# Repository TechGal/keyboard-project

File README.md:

# keyboard-project
Files for my first mechanical keyboard!

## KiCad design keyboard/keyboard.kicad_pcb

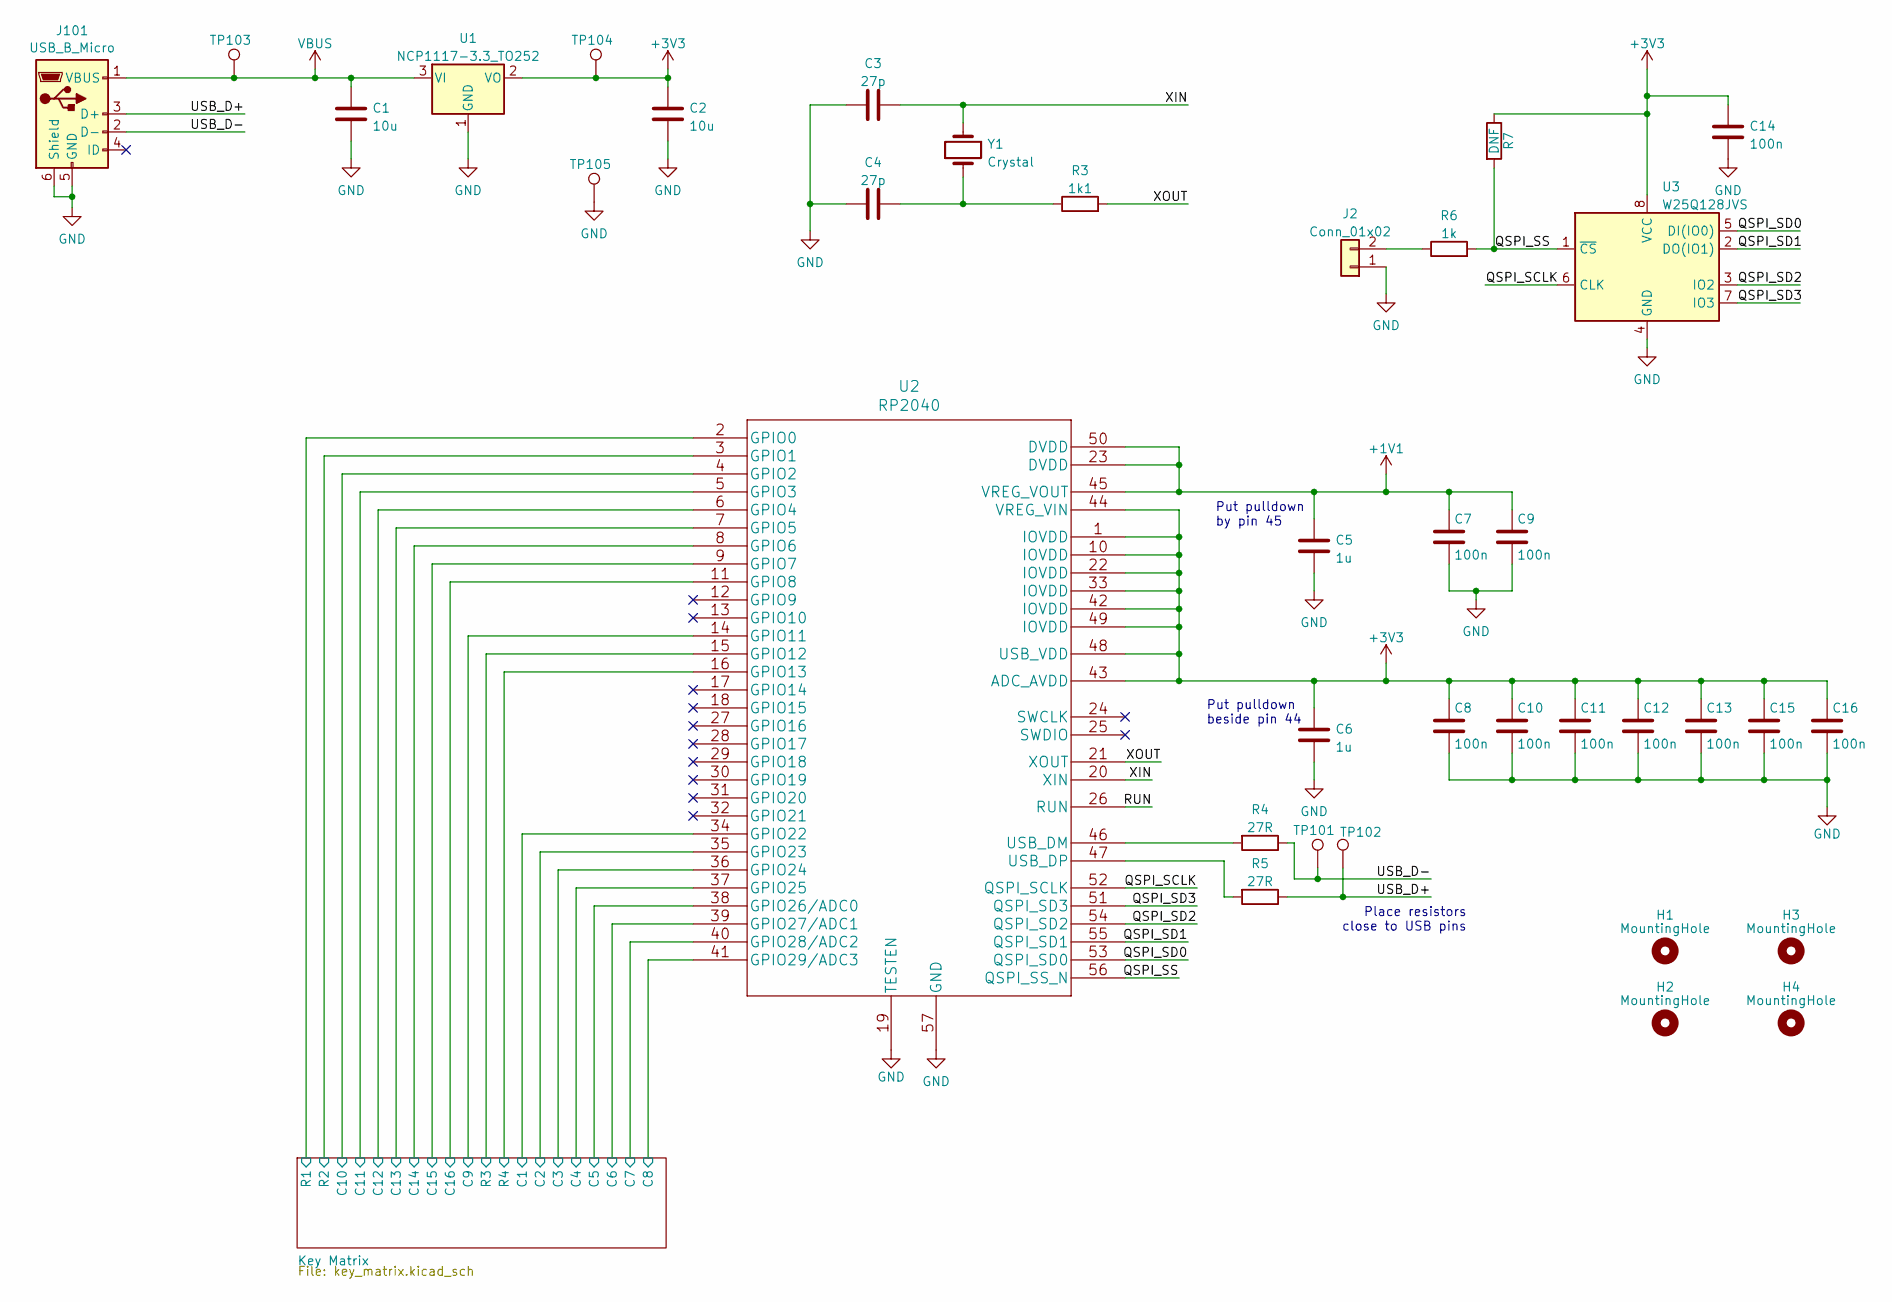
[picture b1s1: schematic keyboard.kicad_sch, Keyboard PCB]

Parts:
C1, C2: 10u; C_0603_1608Metric_Pad1.08x0.95mm_HandSolder
C3, C4: 27p; C_0603_1608Metric_Pad1.08x0.95mm_HandSolder
C5, C6: 1u; C_0603_1608Metric_Pad1.08x0.95mm_HandSolder
C7, C8, C9, C10, C11, C12, C13, C14, C15, C16: 100n; C_0603_1608Metric_Pad1.08x0.95mm_HandSolder
H1, H2, H3, H4: MountingHole; MountingHole_4.3mm_M4_Pad
J2: Conn_01x02; PinHeader_1x02_P2.54mm_Horizontal
J101: USB_B_Micro; USB_Micro-AB_Molex_47590-0001
R3: 1k1; R_0603_1608Metric_Pad0.98x0.95mm_HandSolder
R4, R5: 27R; R_0603_1608Metric_Pad0.98x0.95mm_HandSolder
R6: 1k; R_0603_1608Metric_Pad0.98x0.95mm_HandSolder
R7: DNF; R_0603_1608Metric_Pad0.98x0.95mm_HandSolder
TP101, TP102, TP103, TP104, TP105: TestPoint_THTPad_D1.0mm_Drill0.5mm
U1: NCP1117-3.3_TO252; TO-252-2
U2: RP2040; RP2040-QFN-56
U3: W25Q128JVS; SOIC-8_5.23x5.23mm_P1.27mm
Y1: Crystal; Crystal_HC18-U_Vertical

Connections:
+1V1: C5.1, C7.1, C9.1, U2.23 (DVDD), U2.45 (VREG_VOUT), U2.50 (DVDD)
+3V3: C2.1, C6.1, C8.1, C10.1, C11.1, C12.1, C13.1, C14.1, C15.1, C16.1, R7.1, TP104.1, U1.2 (VO), U2.1 (IOVDD), U2.10 (IOVDD), U2.22 (IOVDD), U2.33 (IOVDD), U2.42 (IOVDD), U2.43 (ADC_AVDD), U2.44 (VREG_VIN), U2.48 (USB_VDD), U2.49 (IOVDD), U3.8 (VCC)
/Key Matrix/C1: U2.34 (GPIO22); also elsewhere on the board
/Key Matrix/C2: U2.35 (GPIO23); also elsewhere on the board
/Key Matrix/C3: U2.36 (GPIO24); also elsewhere on the board
/Key Matrix/C4: U2.37 (GPIO25); also elsewhere on the board
/Key Matrix/C5: U2.38 (GPIO26/ADC0); also elsewhere on the board
/Key Matrix/C6: U2.39 (GPIO27/ADC1); also elsewhere on the board
/Key Matrix/C7: U2.40 (GPIO28/ADC2); also elsewhere on the board
/Key Matrix/C8: U2.41 (GPIO29/ADC3); also elsewhere on the board
/Key Matrix/C9: U2.14 (GPIO11); also elsewhere on the board
/Key Matrix/C10: U2.4 (GPIO2); also elsewhere on the board
/Key Matrix/C11: U2.5 (GPIO3); also elsewhere on the board
/Key Matrix/C12: U2.6 (GPIO4); also elsewhere on the board
/Key Matrix/C13: U2.7 (GPIO5); also elsewhere on the board
/Key Matrix/C14: U2.8 (GPIO6); also elsewhere on the board
/Key Matrix/C15: U2.9 (GPIO7); also elsewhere on the board
/Key Matrix/C16: U2.11 (GPIO8); also elsewhere on the board
/Key Matrix/R1: U2.2 (GPIO0); also elsewhere on the board
/Key Matrix/R2: U2.3 (GPIO1); also elsewhere on the board
/Key Matrix/R3: U2.15 (GPIO12); also elsewhere on the board
/Key Matrix/R4: U2.16 (GPIO13); also elsewhere on the board
/QSPI_SCLK: U2.52 (QSPI_SCLK), U3.6 (CLK)
/QSPI_SD0: U2.53 (QSPI_SD0), U3.5 (DI(IO0))
/QSPI_SD1: U2.55 (QSPI_SD1), U3.2 (DO(IO1))
/QSPI_SD2: U2.54 (QSPI_SD2), U3.3 (IO2)
/QSPI_SD3: U2.51 (QSPI_SD3), U3.7 (IO3)
/QSPI_SS: R6.2, R7.2, U2.56 (QSPI_SS_N), U3.1 (~CS)
/RUN: U2.26 (RUN)
/USB_D+: J101.3 (D+), R5.1, TP102.1
/USB_D-: J101.2 (D-), R4.1, TP101.1
/XIN: C3.2, U2.20 (XIN), Y1.2
/XOUT: R3.2, U2.21 (XOUT)
GND: C1.2, C2.2, C3.1, C4.1, C5.2, C6.2, C7.2, C8.2, C9.2, C10.2, C11.2, C12.2, C13.2, C14.2, C15.2, C16.2, J2.1, J101.5 (GND), J101.6 (Shield), TP105.1, U1.1 (GND), U2.19 (TESTEN), U2.57 (GND), U3.4 (GND)
unnamed: C4.2, R3.1, Y1.1
unnamed: J2.2, R6.1
unnamed: R4.2, U2.46 (USB_DM)
unnamed: R5.2, U2.47 (USB_DP)
VBUS: C1.1, J101.1 (VBUS), TP103.1, U1.3 (VI)

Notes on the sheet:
Put pulldown beside pin 44
Put pulldown by pin 45
Place resistors close to USB pins

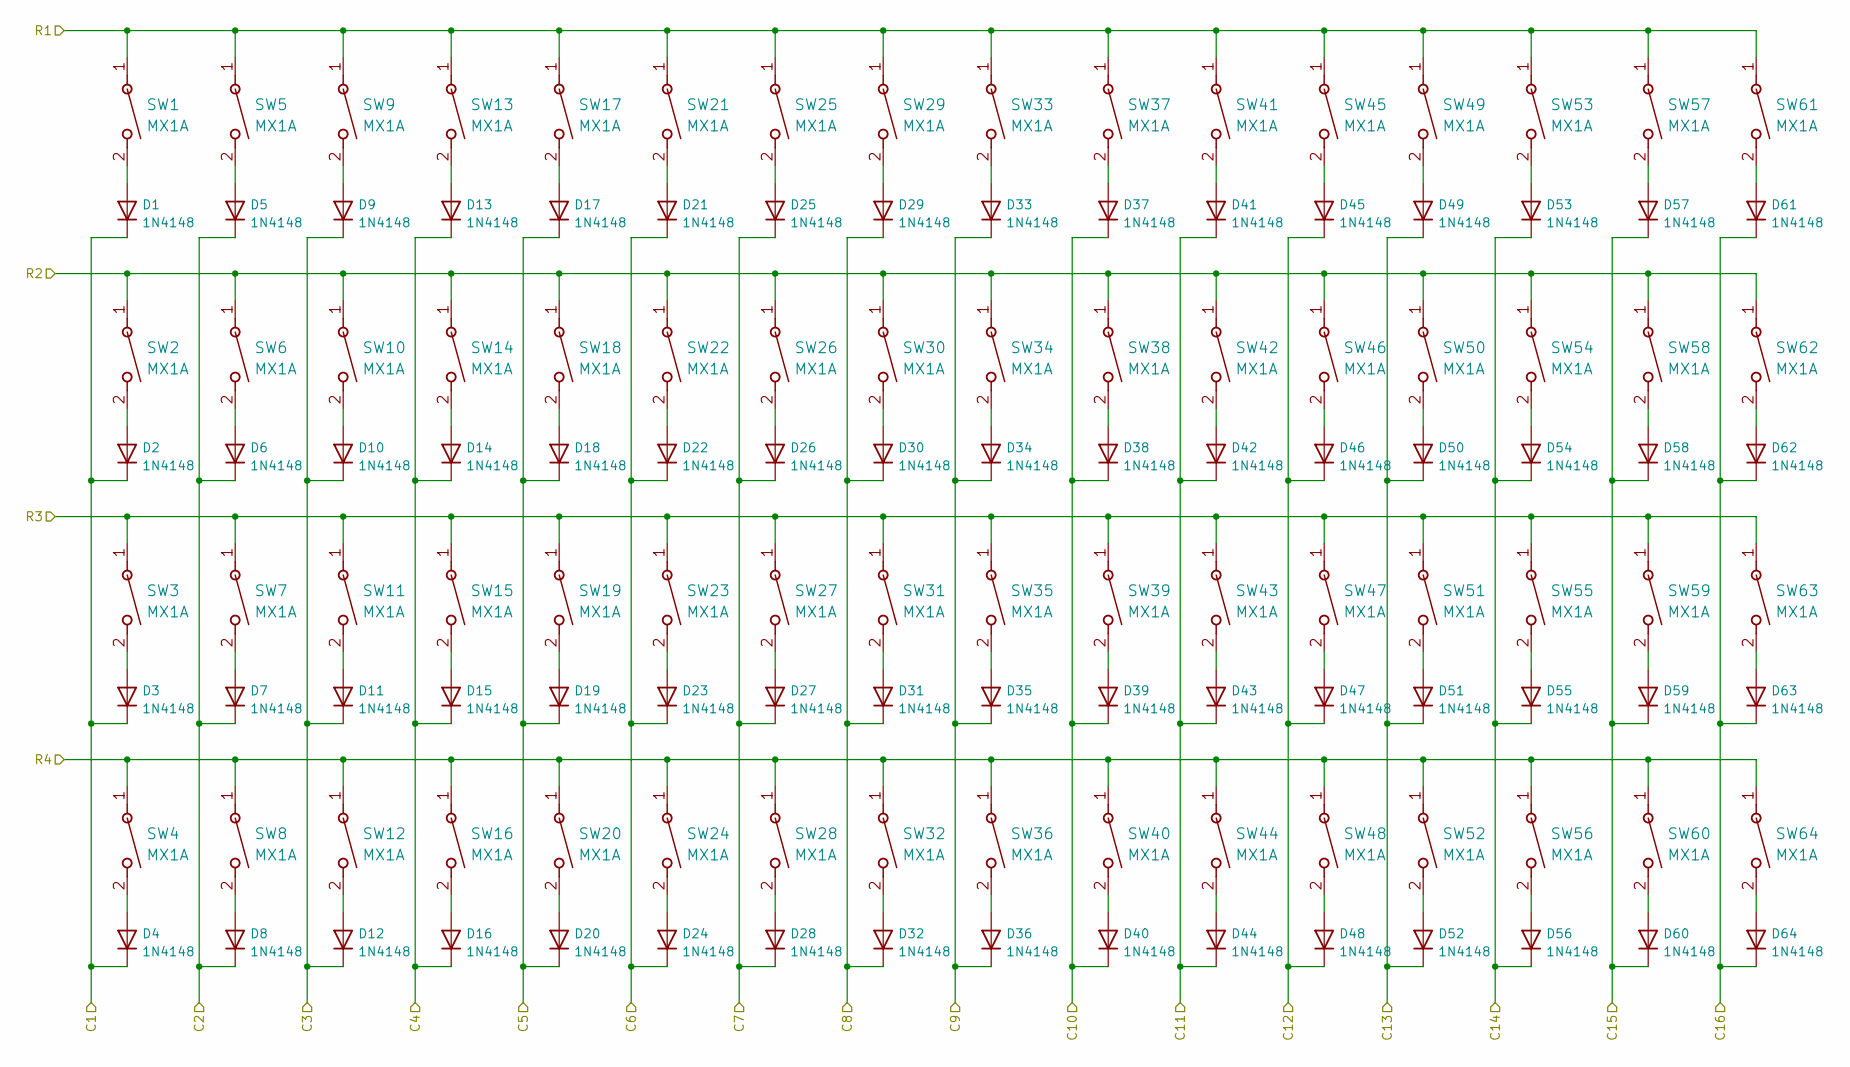
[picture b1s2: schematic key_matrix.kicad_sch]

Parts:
D1, D2, D3, D4, D5, D6, D7, D8, D9, D10, D11, D12, D13, D14, D15, D16, D17, D18, D19, D20, D21, D22, D23, D24, D25, D26, D27, D28, D29, D30, D31, D32, D33, D34, D35, D36, D37, D38, D39, D40, D41, D42, D43, D44, D45, D46, D47, D48, D49, D50, D51, D52, D53, D54, D55, D56, D57, D58, D59, D60, D61, D62, D63, D64: 1N4148; D_0805_2012Metric_Pad1.15x1.40mm_HandSolder
SW1, SW2, SW3, SW4, SW5, SW6, SW7, SW8, SW9, SW10, SW11, SW12, SW13, SW14, SW15, SW16, SW17, SW18, SW19, SW20, SW21, SW22, SW23, SW24, SW25, SW26, SW27, SW28, SW29, SW30, SW31, SW32, SW33, SW34, SW35, SW36, SW37, SW38, SW39, SW40, SW41, SW42, SW43, SW44, SW45, SW46, SW47, SW48, SW49, SW50, SW51, SW52, SW53, SW54, SW55, SW56, SW57, SW58, SW59, SW60, SW61, SW62, SW63, SW64: MX1A; SW_Cherry_MX_1.00u_PCB

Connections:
/Key Matrix/C1: D1.1 (K), D2.1 (K), D3.1 (K), D4.1 (K); also elsewhere on the board
/Key Matrix/C2: D5.1 (K), D6.1 (K), D7.1 (K), D8.1 (K); also elsewhere on the board
/Key Matrix/C3: D9.1 (K), D10.1 (K), D11.1 (K), D12.1 (K); also elsewhere on the board
/Key Matrix/C4: D13.1 (K), D14.1 (K), D15.1 (K), D16.1 (K); also elsewhere on the board
/Key Matrix/C5: D17.1 (K), D18.1 (K), D19.1 (K), D20.1 (K); also elsewhere on the board
/Key Matrix/C6: D21.1 (K), D22.1 (K), D23.1 (K), D24.1 (K); also elsewhere on the board
/Key Matrix/C7: D25.1 (K), D26.1 (K), D27.1 (K), D28.1 (K); also elsewhere on the board
/Key Matrix/C8: D29.1 (K), D30.1 (K), D31.1 (K), D32.1 (K); also elsewhere on the board
/Key Matrix/C9: D33.1 (K), D34.1 (K), D35.1 (K), D36.1 (K); also elsewhere on the board
/Key Matrix/C10: D37.1 (K), D38.1 (K), D39.1 (K), D40.1 (K); also elsewhere on the board
/Key Matrix/C11: D41.1 (K), D42.1 (K), D43.1 (K), D44.1 (K); also elsewhere on the board
/Key Matrix/C12: D45.1 (K), D46.1 (K), D47.1 (K), D48.1 (K); also elsewhere on the board
/Key Matrix/C13: D49.1 (K), D50.1 (K), D51.1 (K), D52.1 (K); also elsewhere on the board
/Key Matrix/C14: D53.1 (K), D54.1 (K), D55.1 (K), D56.1 (K); also elsewhere on the board
/Key Matrix/C15: D57.1 (K), D58.1 (K), D59.1 (K), D60.1 (K); also elsewhere on the board
/Key Matrix/C16: D61.1 (K), D62.1 (K), D63.1 (K), D64.1 (K); also elsewhere on the board
/Key Matrix/R1: SW1.1, SW5.1, SW9.1, SW13.1, SW17.1, SW21.1, SW25.1, SW29.1, SW33.1, SW37.1, SW41.1, SW45.1, SW49.1, SW53.1, SW57.1, SW61.1; also elsewhere on the board
/Key Matrix/R2: SW2.1, SW6.1, SW10.1, SW14.1, SW18.1, SW22.1, SW26.1, SW30.1, SW34.1, SW38.1, SW42.1, SW46.1, SW50.1, SW54.1, SW58.1, SW62.1; also elsewhere on the board
/Key Matrix/R3: SW3.1, SW7.1, SW11.1, SW15.1, SW19.1, SW23.1, SW27.1, SW31.1, SW35.1, SW39.1, SW43.1, SW47.1, SW51.1, SW55.1, SW59.1, SW63.1; also elsewhere on the board
/Key Matrix/R4: SW4.1, SW8.1, SW12.1, SW16.1, SW20.1, SW24.1, SW28.1, SW32.1, SW36.1, SW40.1, SW44.1, SW48.1, SW52.1, SW56.1, SW60.1, SW64.1; also elsewhere on the board
unnamed: D1.2 (A), SW1.2
unnamed: D2.2 (A), SW2.2
unnamed: D3.2 (A), SW3.2
unnamed: D4.2 (A), SW4.2
unnamed: D5.2 (A), SW5.2
unnamed: D6.2 (A), SW6.2
unnamed: D7.2 (A), SW7.2
unnamed: D8.2 (A), SW8.2
unnamed: D9.2 (A), SW9.2
unnamed: D10.2 (A), SW10.2
unnamed: D11.2 (A), SW11.2
unnamed: D12.2 (A), SW12.2
unnamed: D13.2 (A), SW13.2
unnamed: D14.2 (A), SW14.2
unnamed: D15.2 (A), SW15.2
unnamed: D16.2 (A), SW16.2
unnamed: D17.2 (A), SW17.2
unnamed: D18.2 (A), SW18.2
unnamed: D19.2 (A), SW19.2
unnamed: D20.2 (A), SW20.2
unnamed: D21.2 (A), SW21.2
unnamed: D22.2 (A), SW22.2
unnamed: D23.2 (A), SW23.2
unnamed: D24.2 (A), SW24.2
unnamed: D25.2 (A), SW25.2
unnamed: D26.2 (A), SW26.2
unnamed: D27.2 (A), SW27.2
unnamed: D28.2 (A), SW28.2
unnamed: D29.2 (A), SW29.2
unnamed: D30.2 (A), SW30.2
unnamed: D31.2 (A), SW31.2
unnamed: D32.2 (A), SW32.2
unnamed: D33.2 (A), SW33.2
unnamed: D34.2 (A), SW34.2
unnamed: D35.2 (A), SW35.2
unnamed: D36.2 (A), SW36.2
unnamed: D37.2 (A), SW37.2
unnamed: D38.2 (A), SW38.2
unnamed: D39.2 (A), SW39.2
unnamed: D40.2 (A), SW40.2
unnamed: D41.2 (A), SW41.2
unnamed: D42.2 (A), SW42.2
unnamed: D43.2 (A), SW43.2
unnamed: D44.2 (A), SW44.2
unnamed: D45.2 (A), SW45.2
unnamed: D46.2 (A), SW46.2
unnamed: D47.2 (A), SW47.2
unnamed: D48.2 (A), SW48.2
unnamed: D49.2 (A), SW49.2
unnamed: D50.2 (A), SW50.2
unnamed: D51.2 (A), SW51.2
unnamed: D52.2 (A), SW52.2
unnamed: D53.2 (A), SW53.2
unnamed: D54.2 (A), SW54.2
unnamed: D55.2 (A), SW55.2
unnamed: D56.2 (A), SW56.2
unnamed: D57.2 (A), SW57.2
unnamed: D58.2 (A), SW58.2
unnamed: D59.2 (A), SW59.2
unnamed: D60.2 (A), SW60.2
unnamed: D61.2 (A), SW61.2
unnamed: D62.2 (A), SW62.2
unnamed: D63.2 (A), SW63.2
unnamed: D64.2 (A), SW64.2

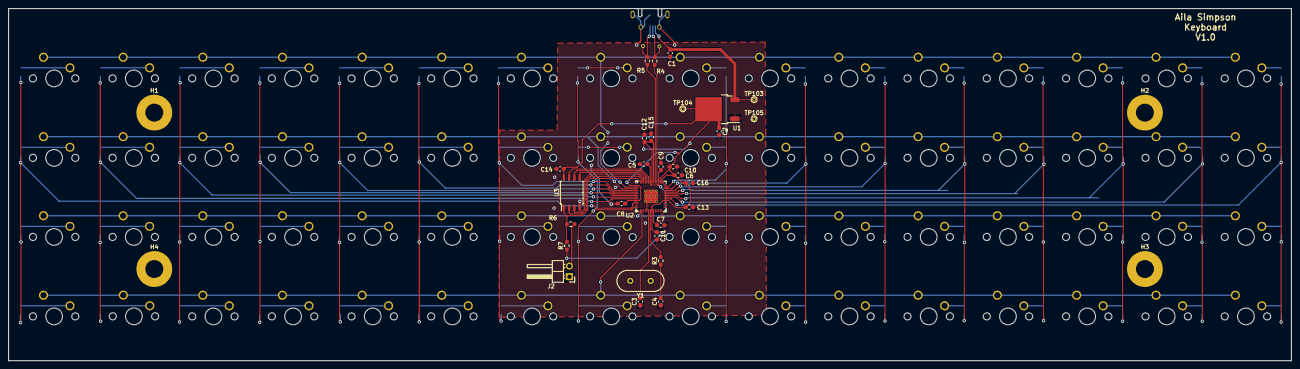
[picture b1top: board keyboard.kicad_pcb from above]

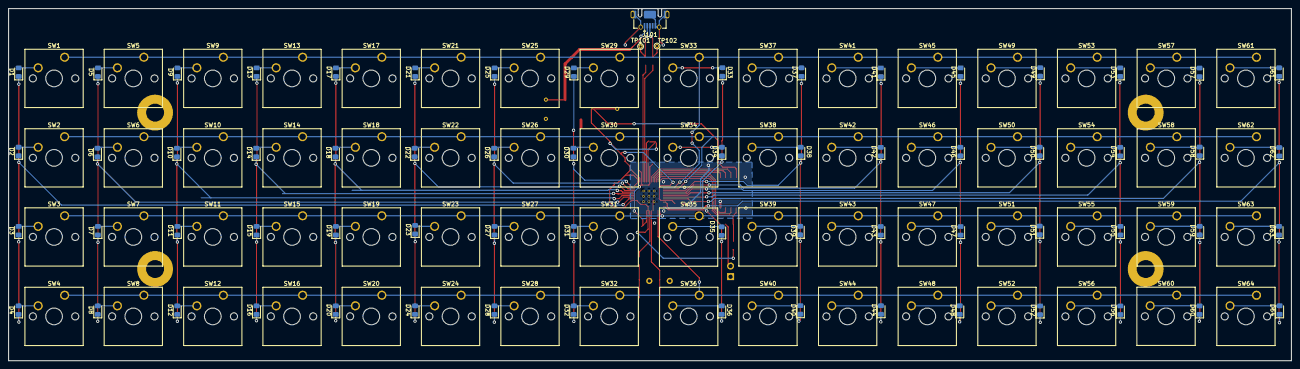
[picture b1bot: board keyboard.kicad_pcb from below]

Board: 2 copper layers, 307.6 x 84.4 mm, 164 parts (131 on the bottom side), 102 nets.

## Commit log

2021-11-26 first commit, adding files from computer
2025-08-13 V2 of the keyboard hardware files
